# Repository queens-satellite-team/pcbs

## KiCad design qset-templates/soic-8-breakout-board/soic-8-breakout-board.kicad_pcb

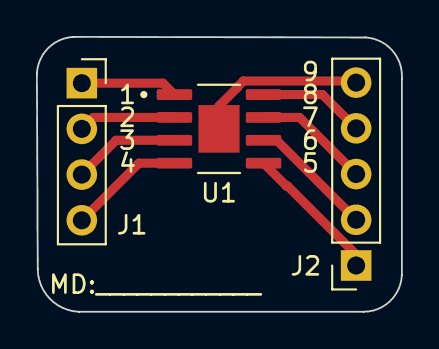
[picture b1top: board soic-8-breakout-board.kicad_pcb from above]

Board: 2 copper layers, 20.3 x 15.3 mm, 3 parts (0 on the bottom side), 9 nets.

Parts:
J1: Conn_01x04_Female; PinSocket_1x04_P2.54mm_Vertical
J2: Conn_01x05_Female; PinSocket_1x05_P2.54mm_Vertical
U1: ADP7158ARDZ-3.3-R7; SOIC127P600X175-9N

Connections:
unnamed: J1.1, U1.1 (VOUT)
unnamed: J1.2, U1.2 (VOUT_SENSE)
unnamed: J1.3, U1.3 (BYP)
unnamed: J1.4, U1.4 (EN)
unnamed: J2.1, U1.5 (REF_SENSE)
unnamed: J2.2, U1.6 (REF)
unnamed: J2.3, U1.7 (VREG)
unnamed: J2.4, U1.8 (VIN)
unnamed: J2.5, U1.9 (EPAD)
